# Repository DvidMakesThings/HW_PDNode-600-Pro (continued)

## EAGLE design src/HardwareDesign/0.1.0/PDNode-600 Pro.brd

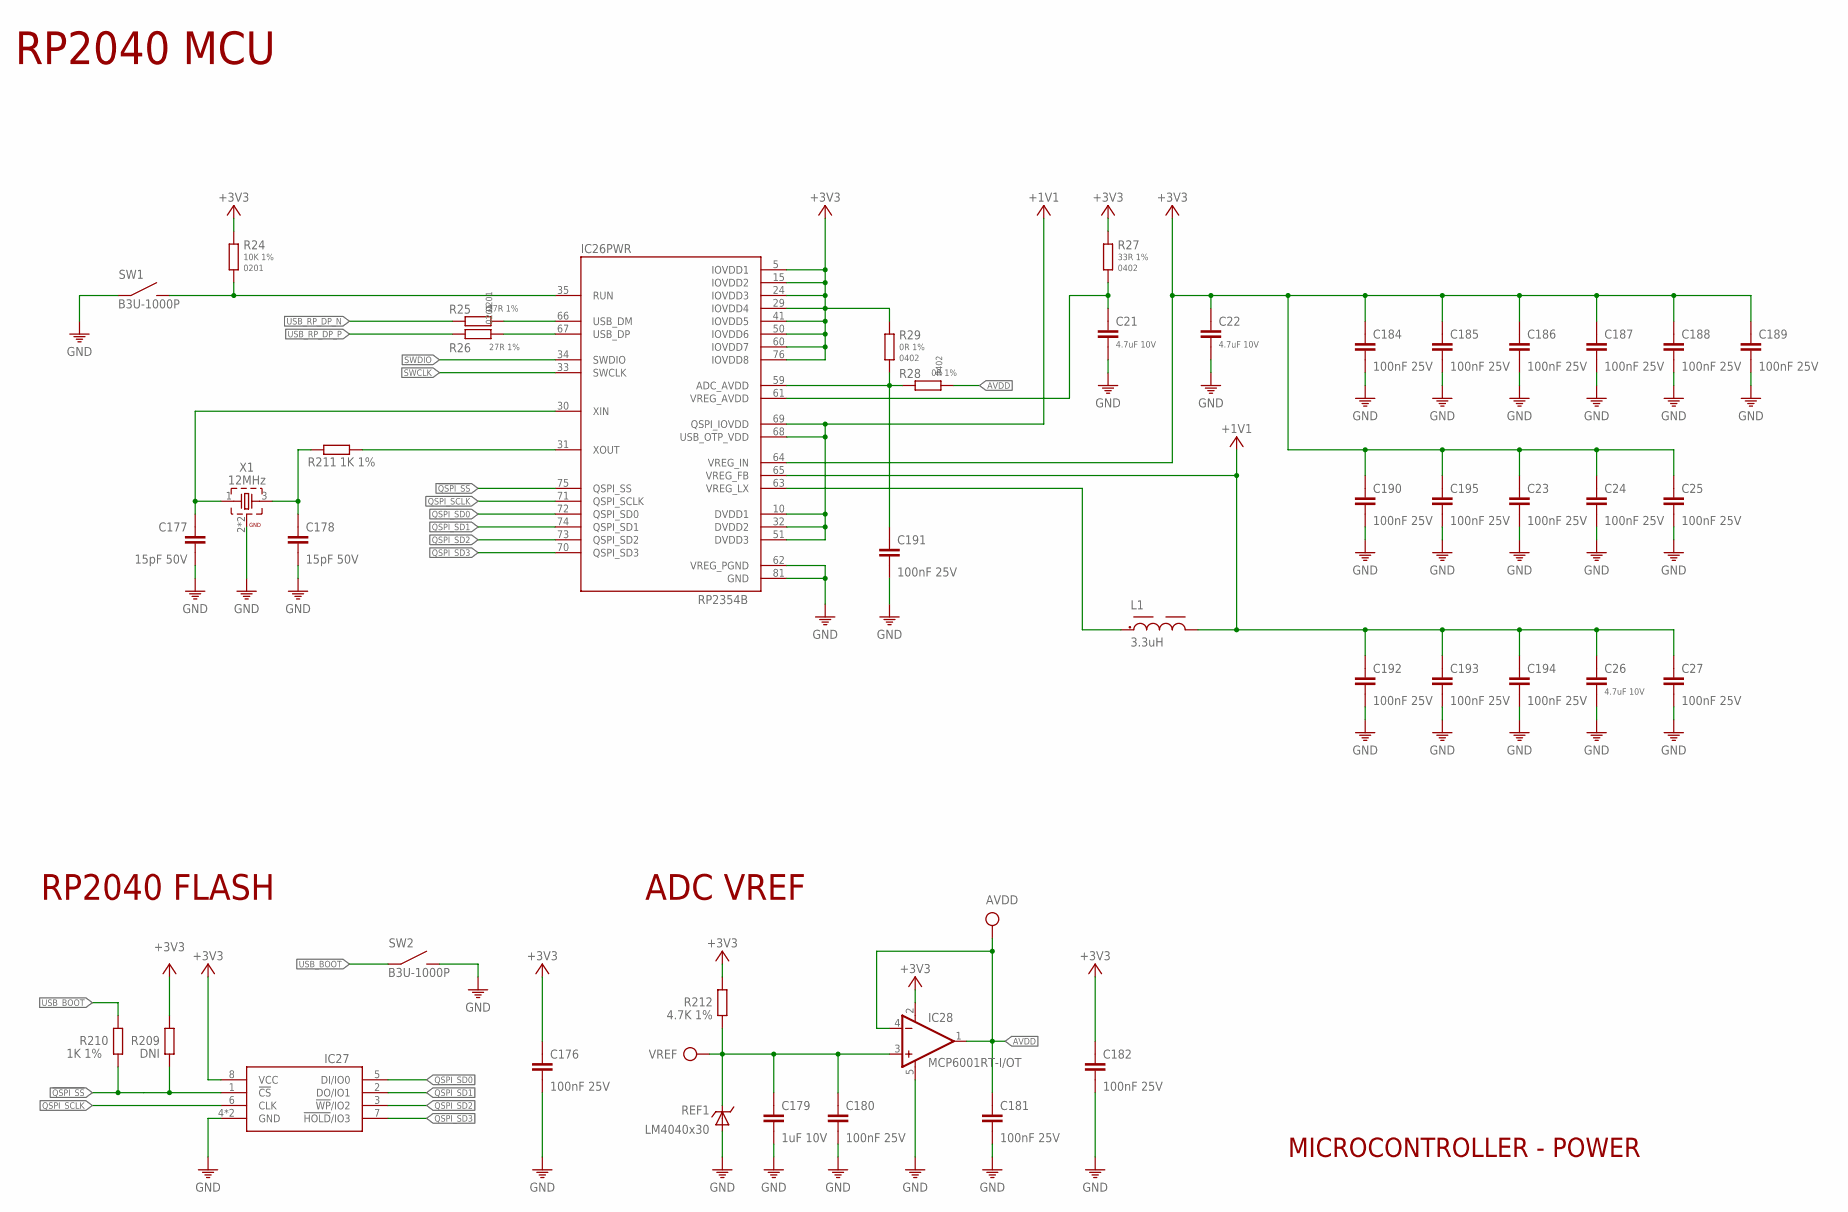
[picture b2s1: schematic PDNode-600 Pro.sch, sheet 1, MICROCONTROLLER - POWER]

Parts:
AVDD: TESTPOINT; TP
C21, C22, C26: 4.7uF 10V; 0402
C23, C24, C25, C27, C176, C180, C181, C182, C184, C185, C186, C187, C188, C189, C190, C191, C192, C193, C194, C195: 100nF 25V; 0201
C177, C178: 15pF 50V; 0201
C179: 1uF 10V; 0201
IC26: RP2354B; QFN80-10X10
IC27: W25Q128JVPIQ; SON127P600X500X75-8N
IC28: MCP6001RT-I/OT; SOT23-5
L1: 3.3uH; 0805
R24: 10K 1%; 0201
R25, R26: 27R 1%; 0201
R27: 33R 1%; 0402
R28, R29: 0R 1%; 0402
R209: DNI; R0201
R210, R211: 1K 1%; 0201
R212: 4.7K 1%; 0201
REF1: LM4040x30; SOT23
SW1, SW2: B3U-1000P
VREF: TESTPOINT; TP
X1: 12MHz; WE-XTAL_CFPX-180

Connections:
!QSPI_SS: IC26.75 (QSPI_SS), IC27.1 (!CS), R209.1, R210.2
+1V1: C26.1, C27.1, C192.1, C193.1, C194.1, IC26.10 (DVDD1), IC26.32 (DVDD2), IC26.51 (DVDD3), IC26.65 (VREG_FB), IC26.68 (USB_OTP_VDD), IC26.69 (QSPI_IOVDD), L1.2
+3V3: C22.1, C23.1, C24.1, C25.1, C176.1, C182.1, C184.1, C185.1, C186.1, C187.1, C188.1, C189.1, C190.1, C195.1, IC26.5 (IOVDD1), IC26.15 (IOVDD2), IC26.24 (IOVDD3), IC26.29 (IOVDD4), IC26.41 (IOVDD5), IC26.50 (IOVDD6), IC26.60 (IOVDD7), IC26.64 (VREG_IN), IC26.76 (IOVDD8), IC27.8 (VCC), IC28.2 (V+), R24.1, R27.1, R29.1, R209.2, R212.2; also elsewhere on the board
AVDD: AVDD.TP, C181.1, IC28.1 (OUT), IC28.4 (-IN), R28.2
GND: C21.2, C22.2, C23.2, C24.2, C25.2, C26.2, C27.2, C176.2, C177.2, C178.2, C179.2, C180.2, C181.2, C182.2, C184.2, C185.2, C186.2, C187.2, C188.2, C189.2, C190.2, C191.2, C192.2, C193.2, C194.2, C195.2, IC26.62 (VREG_PGND), IC26.81 (GND), IC27.4 (GND), IC27.PAD (GND), IC28.5 (V-), REF1.2 (A), REF1.3 (A), SW1.1, SW2.2, X1.2 (GND), X1.4 (GND); also elsewhere on the board
unnamed: IC26.35 (RUN), R24.2, SW1.2
unnamed: IC26.66 (USB_DM), R25.2
unnamed: IC26.67 (USB_DP), R26.2
unnamed: C191.1, IC26.59 (ADC_AVDD), R28.1, R29.2
unnamed: C21.1, IC26.61 (VREG_AVDD), R27.2
unnamed: IC26.63 (VREG_LX), L1.1
unnamed: C178.1, R211.1, X1.3 (2)
QSPI_SCLK: IC26.71 (QSPI_SCLK), IC27.6 (CLK)
QSPI_SD0: IC26.72 (QSPI_SD0), IC27.5 (DI/IO0)
QSPI_SD1: IC26.74 (QSPI_SD1), IC27.2 (DO/IO1)
QSPI_SD2: IC26.73 (QSPI_SD2), IC27.3 (!WP!/IO2)
QSPI_SD3: IC26.70 (QSPI_SD3), IC27.7 (!HOLD!/IO3)
RP_XI: C177.1, IC26.30 (XIN), X1.1
RP_XO: IC26.31 (XOUT), R211.2
SWCLK: IC26.33 (SWCLK)
SWDIO: IC26.34 (SWDIO)
USB_BOOT: R210.1, SW2.1
USB_RP_DP_N: R25.1
USB_RP_DP_P: R26.1
VREF: C179.1, C180.1, IC28.3 (+IN), R212.1, REF1.1 (C), VREF.TP

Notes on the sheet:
RP2040 MCU
RP2040 FLASH
ADC VREF
MICROCONTROLLER - POWER

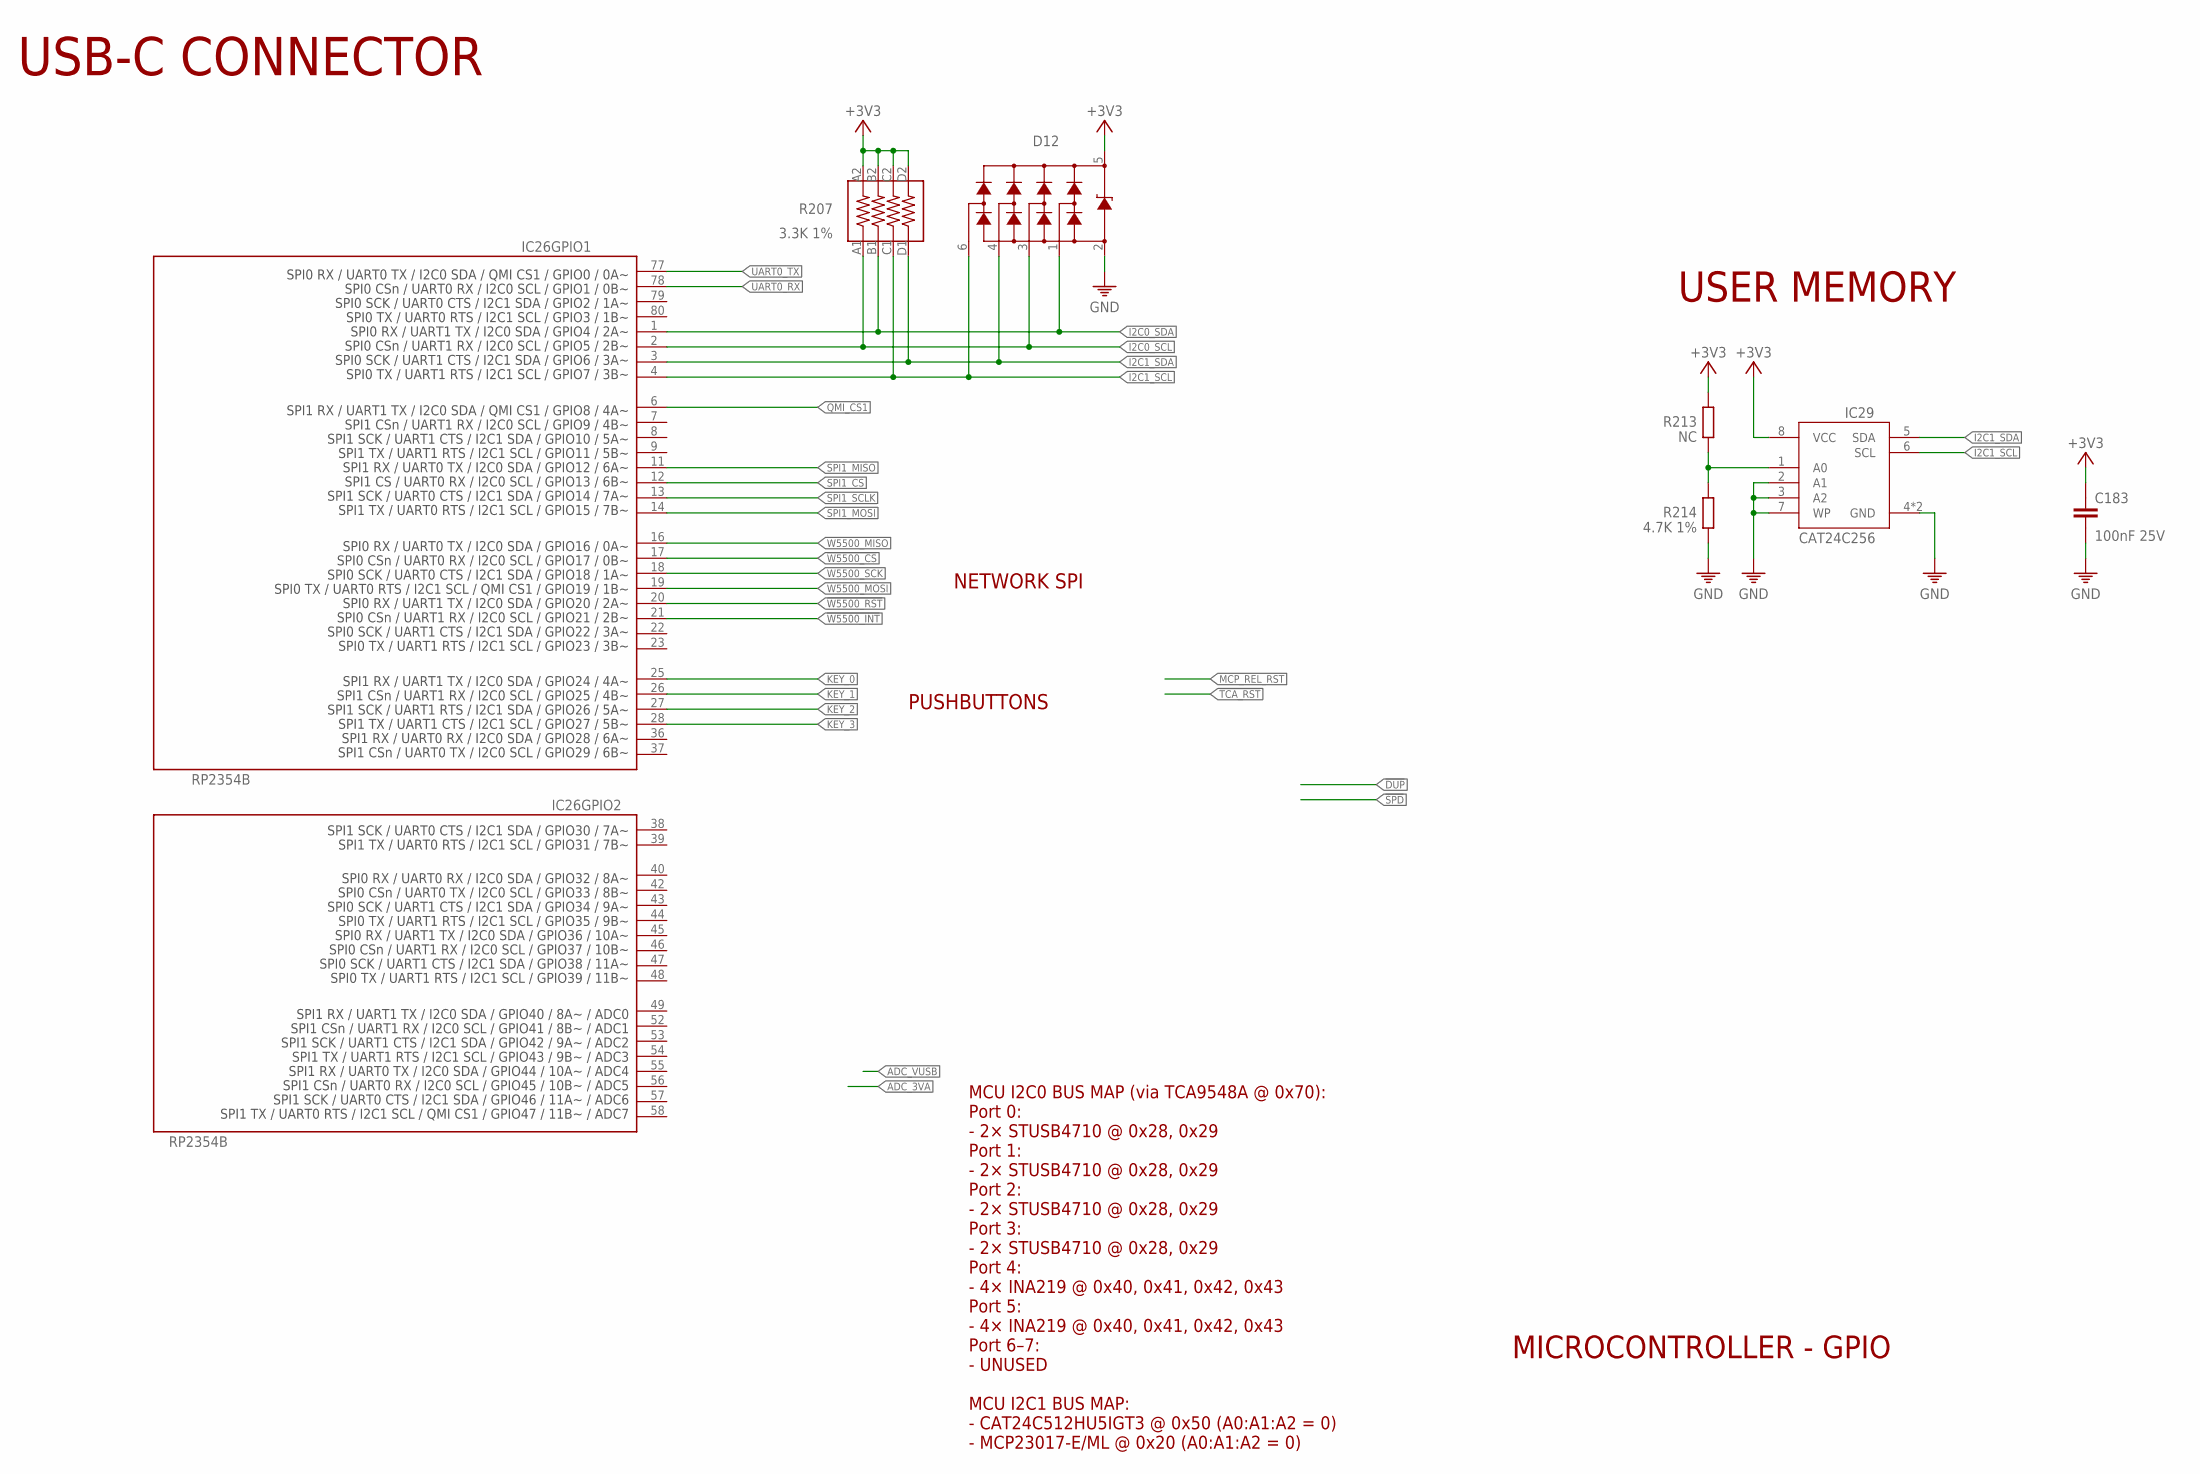
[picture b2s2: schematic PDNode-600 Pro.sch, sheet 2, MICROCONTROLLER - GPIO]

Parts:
C183: 100nF 25V; 0201
D12: HDMIULC6-4SC6Y; SOT23-6
IC26: RP2354B; QFN80-10X10
IC29: CAT24C256HU4IGT3; SON50P300X200X50-9T130X140N
R207: 3.3K 1%; _0603X4-1206
R213: NC; R0201
R214: 4.7K 1%; 0201

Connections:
!W5500_CS: IC26.17 (GPIO17); also elsewhere on the board
!W5500_INT: IC26.21 (GPIO21); also elsewhere on the board
!W5500_RST: IC26.20 (GPIO20); also elsewhere on the board
+3V3: C183.1, D12.5, IC29.8 (VCC), R207.A2 (8), R207.B2 (7), R207.C2 (6), R207.D2 (5), R213.2; also elsewhere on the board
GND: C183.2, D12.2, IC29.2 (A1), IC29.3 (A2), IC29.4 (GND), IC29.7 (WP), IC29.9 (GND), R214.1; also elsewhere on the board
I2C0_SCL: D12.3, IC26.2 (GPIO5), R207.A1 (1); also elsewhere on the board
I2C0_SDA: D12.1, IC26.1 (GPIO4), R207.B1 (2); also elsewhere on the board
I2C1_SCL: D12.6, IC26.4 (GPIO7), IC29.6 (SCL), R207.C1 (3); also elsewhere on the board
I2C1_SDA: D12.4, IC26.3 (GPIO6), IC29.5 (SDA), R207.D1 (4); also elsewhere on the board
KEY_0: IC26.25 (GPIO24); also elsewhere on the board
KEY_1: IC26.26 (GPIO25); also elsewhere on the board
KEY_2: IC26.27 (GPIO26); also elsewhere on the board
KEY_3: IC26.28 (GPIO27); also elsewhere on the board
unnamed: IC29.1 (A0), R213.1, R214.2
QMI_CS1: IC26.6 (GPIO8)
SPI1_CS: IC26.12 (GPIO13)
SPI1_MISO: IC26.11 (GPIO12)
SPI1_MOSI: IC26.14 (GPIO15)
SPI1_SCLK: IC26.13 (GPIO14)
UART0_RX: IC26.78 (GPIO1)
UART0_TX: IC26.77 (GPIO0)
W5500_MISO: IC26.16 (GPIO16); also elsewhere on the board
W5500_MOSI: IC26.19 (GPIO19); also elsewhere on the board
W5500_SCK: IC26.18 (GPIO18); also elsewhere on the board

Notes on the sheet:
USB-C CONNECTOR
NETWORK SPI
PUSHBUTTONS
MCU I2C0 BUS MAP (via TCA9548A @ 0x70): Port 0: - 2× STUSB4710 @ 0x28, 0x29 Port 1: - 2× STUSB4710 @ 0x28, 0x29 Port 2: - 2× STUSB4710 @ 0x28, 0x29 Port 3: - 2× STUSB4710 @ 0x28, 0x29 Port 4: - 4× INA219 @ 0x40, 0x41, 0x42, 0x43 Port 5: - 4× INA219 @ 0x40, 0x41, 0x42, 0x43 Port 6–7: - UNUSED MCU I2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
USER MEMORY
MICROCONTROLLER - GPIO

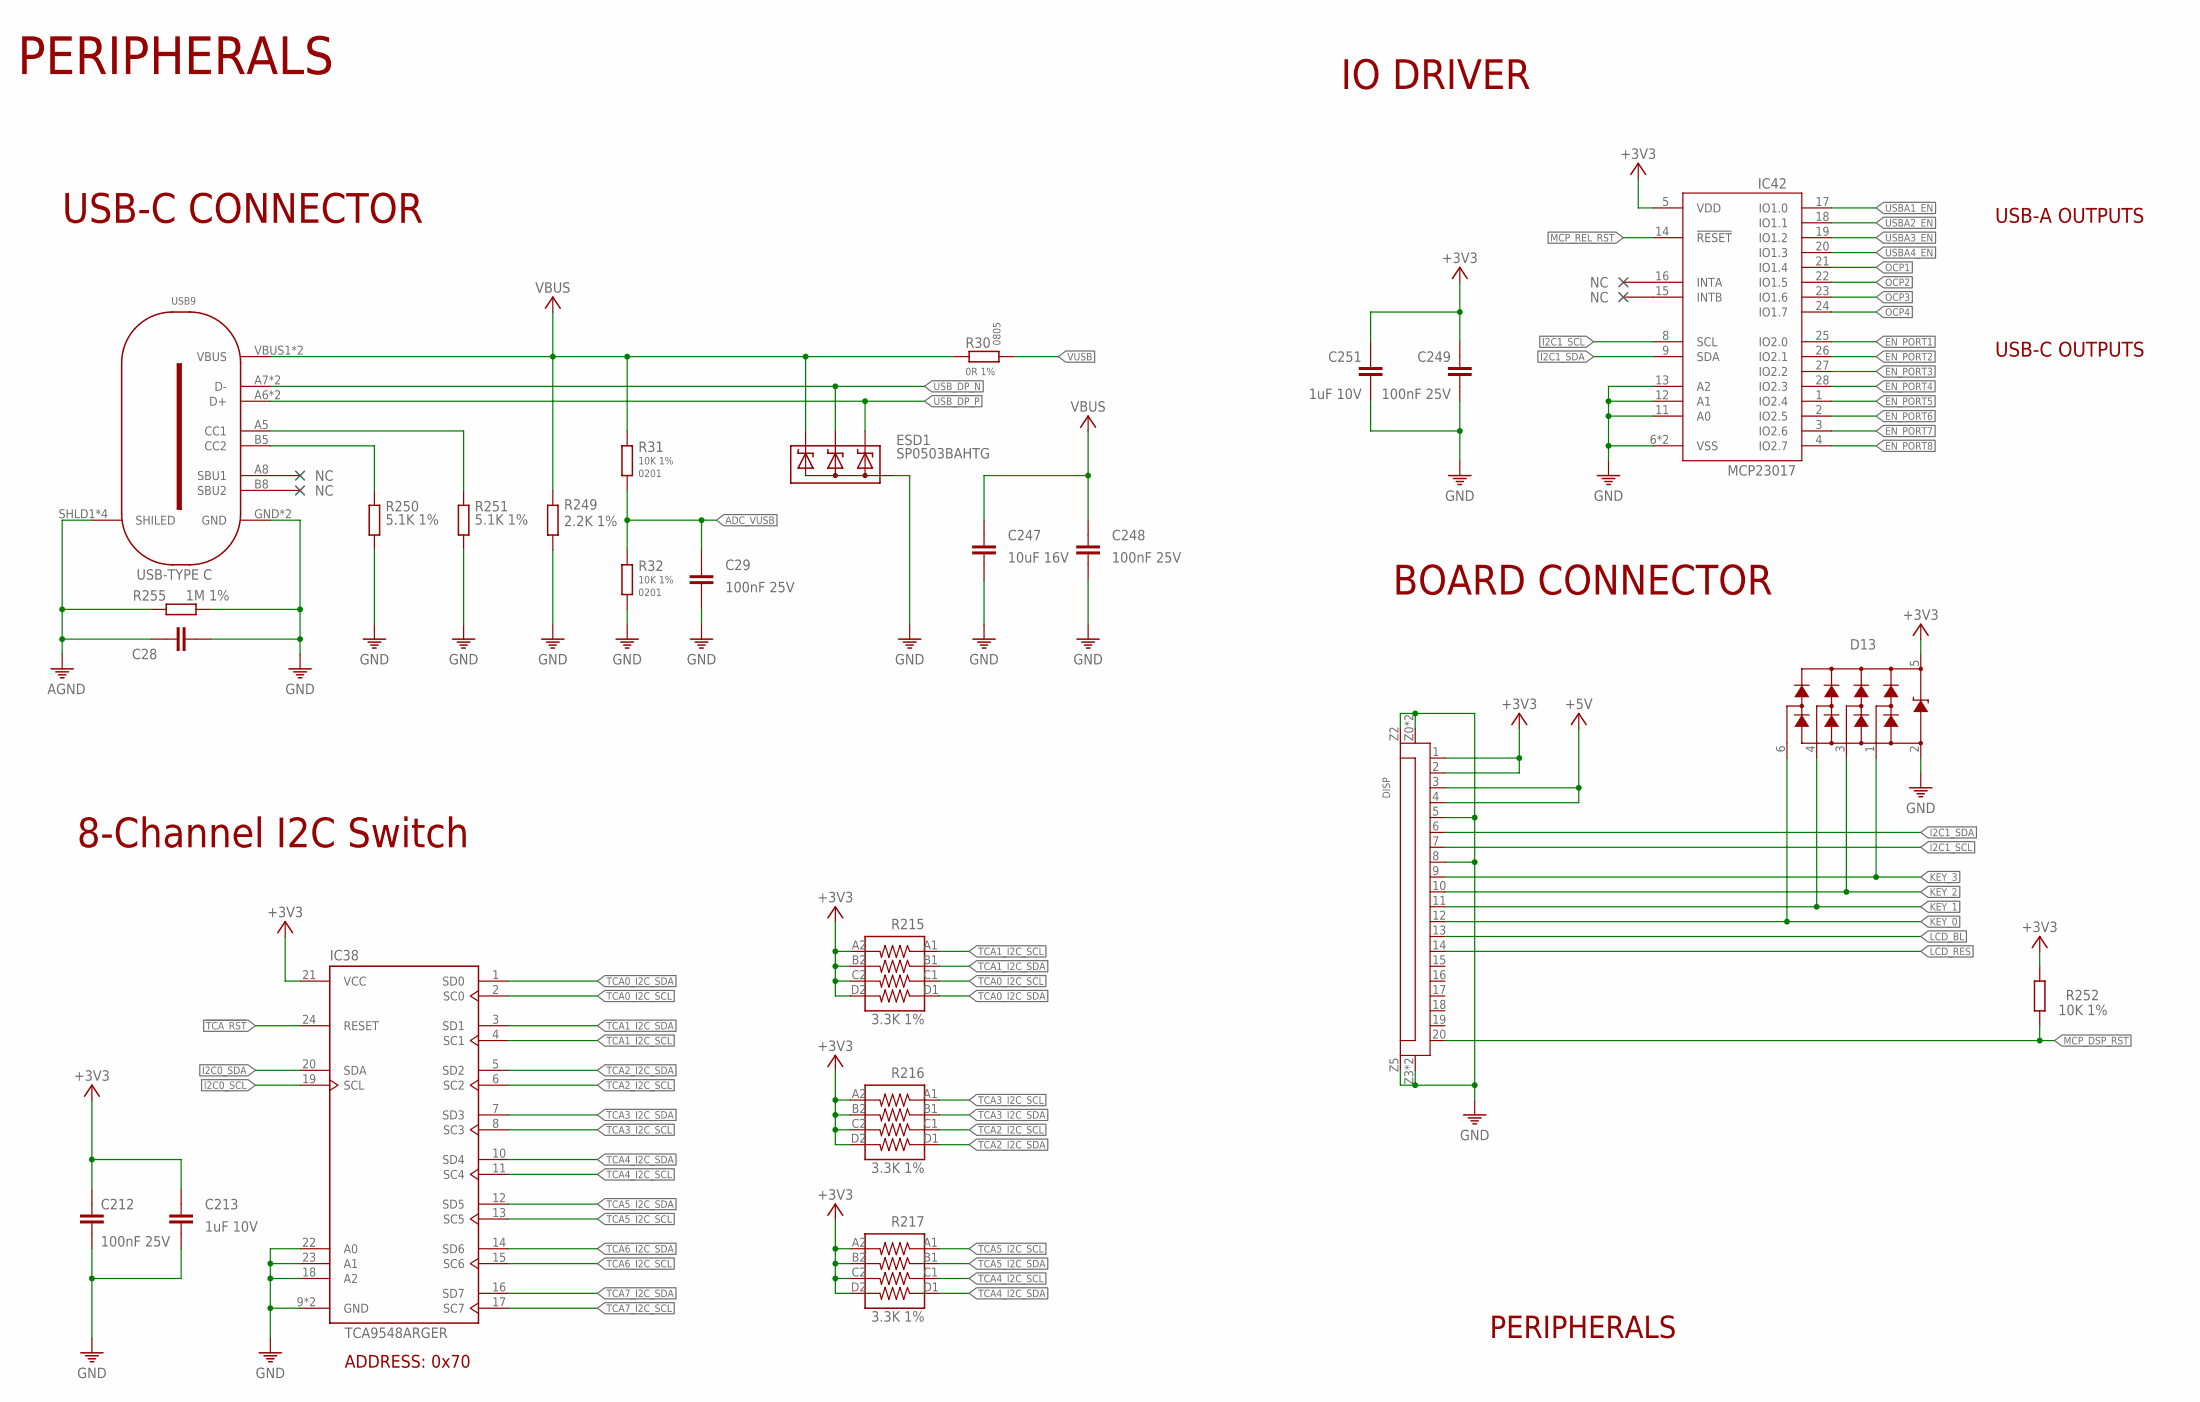
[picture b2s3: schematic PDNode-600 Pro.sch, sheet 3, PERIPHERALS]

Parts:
C28: 1NF-2KV; 1206
C29, C248: 100nF 25V; 0402
C212, C249: 100nF 25V; 0201
C213, C251: 1uF 10V; 0201
C247: 10uF 16V; 0603
D13: HDMIULC6-4SC6Y; SOT23-6
DISP: AFC11-S20ICC-00; FPC20
ESD1: SP0503BAHTG; SOT143
IC38: TCA9548ARGER; QFN50P400X400X100-25T210N
IC42: MCP23017T-E/ML; QFN28[6X6]ML
R30: 0R 1%; 0805
R31, R32, R252: 10K 1%; 0201
R215, R216, R217: 3.3K 1%; _0603X4-1206
R249: 2.2K 1%; 0201
R250, R251: 5.1K 1%; 0201
R255: 1M 1%; 0603
USB9: USB-TYPE-C-018; USB-C

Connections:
!TCA_RST: IC38.24 (RESET)
+3V3: C212.1, C213.1, C249.1, C251.1, D13.5, DISP.1, DISP.2, IC38.21 (VCC), IC42.5 (VDD), R215.A2 (8), R215.B2 (7), R215.C2 (6), R215.D2 (5), R216.A2 (8), R216.B2 (7), R216.C2 (6), R216.D2 (5), R217.A2 (8), R217.B2 (7), R217.C2 (6), R217.D2 (5), R252.2; also elsewhere on the board
+5V: DISP.3, DISP.4
ADC_VUSB: C29.1, R31.2, R32.1
AGND: C28.1, R255.1, USB9.SHLD1 (SHILED), USB9.SHLD2 (SHILED), USB9.SHLD3 (SHILED), USB9.SHLD4 (SHILED); also elsewhere on the board
CC1: R251.1, USB9.A5 (CC1)
CC2: R250.1, USB9.B5 (CC2)
EN_PORT1: IC42.25 (IO2.0); also elsewhere on the board
EN_PORT2: IC42.26 (IO2.1)
EN_PORT3: IC42.27 (IO2.2)
EN_PORT4: IC42.28 (IO2.3)
EN_PORT5: IC42.1 (IO2.4)
EN_PORT6: IC42.2 (IO2.5)
EN_PORT7: IC42.3 (IO2.6)
EN_PORT8: IC42.4 (IO2.7)
GND: C28.2, C29.2, C212.2, C213.2, C247.2, C248.2, C249.2, C251.2, D13.2, DISP.5, DISP.8, DISP.Z0 (Z1), DISP.Z1, DISP.Z2, DISP.Z3, DISP.Z4 (Z3), DISP.Z5 (Z4), ESD1.1 (A), IC38.9 (GND), IC38.18 (A2), IC38.22 (A0), IC38.23 (A1), IC38.25 (GND), IC42.6 (VSS), IC42.11 (A0), IC42.12 (A1), IC42.13 (A2), IC42.PAD (VSS), R32.2, R249.2, R250.2, R251.2, R255.2, USB9.GND, USB9.GND2 (GND); also elsewhere on the board
I2C0_SCL: IC38.19 (SCL); also elsewhere on the board
I2C0_SDA: IC38.20 (SDA); also elsewhere on the board
I2C1_SCL: DISP.7, IC42.8 (SCL); also elsewhere on the board
I2C1_SDA: DISP.6, IC42.9 (SDA); also elsewhere on the board
KEY_0: D13.6, DISP.12; also elsewhere on the board
KEY_1: D13.4, DISP.11; also elsewhere on the board
KEY_2: D13.3, DISP.10; also elsewhere on the board
KEY_3: D13.1, DISP.9; also elsewhere on the board
LCD_BL: DISP.13
LCD_RES: DISP.14
MCP_DSP_RST: DISP.20, R252.1
MCP_REL_RST: IC42.14 (!RESET)
OCP1: IC42.21 (IO1.4); also elsewhere on the board
OCP2: IC42.22 (IO1.5); also elsewhere on the board
OCP3: IC42.23 (IO1.6); also elsewhere on the board
OCP4: IC42.24 (IO1.7); also elsewhere on the board
TCA0_I2C_SCL: IC38.2 (SC0), R215.C1 (3); also elsewhere on the board
TCA0_I2C_SDA: IC38.1 (SD0), R215.D1 (4); also elsewhere on the board
TCA1_I2C_SCL: IC38.4 (SC1), R215.A1 (1)
TCA1_I2C_SDA: IC38.3 (SD1), R215.B1 (2)
TCA2_I2C_SCL: IC38.6 (SC2), R216.C1 (3)
TCA2_I2C_SDA: IC38.5 (SD2), R216.D1 (4)
TCA3_I2C_SCL: IC38.8 (SC3), R216.A1 (1)
TCA3_I2C_SDA: IC38.7 (SD3), R216.B1 (2)
TCA4_I2C_SCL: IC38.11 (SC4), R217.C1 (3); also elsewhere on the board
TCA4_I2C_SDA: IC38.10 (SD4), R217.D1 (4); also elsewhere on the board
TCA5_I2C_SCL: IC38.13 (SC5), R217.A1 (1)
TCA5_I2C_SDA: IC38.12 (SD5), R217.B1 (2)
TCA6_I2C_SCL: IC38.15 (SC6)
TCA6_I2C_SDA: IC38.14 (SD6)
TCA7_I2C_SCL: IC38.17 (SC7)
TCA7_I2C_SDA: IC38.16 (SD7)
USBA1_EN: IC42.17 (IO1.0); also elsewhere on the board
USBA2_EN: IC42.18 (IO1.1); also elsewhere on the board
USBA3_EN: IC42.19 (IO1.2); also elsewhere on the board
USBA4_EN: IC42.20 (IO1.3); also elsewhere on the board
USB_DP_N: ESD1.3 (C2), USB9.A7 (D-), USB9.B7 (D-)
USB_DP_P: ESD1.2 (C1), USB9.A6 (D+), USB9.B6 (D+)
VBUS: C247.1, C248.1, ESD1.4 (C3), R30.1, R31.1, R249.1, USB9.VBUS1 (VBUS), USB9.VBUS2 (VBUS)
VUSB: R30.2

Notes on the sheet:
PERIPHERALS
USB-C CONNECTOR
8-Channel I2C Switch
ADDRESS: 0x70
IO DRIVER
USB-A OUTPUTS
USB-C OUTPUTS
BOARD CONNECTOR

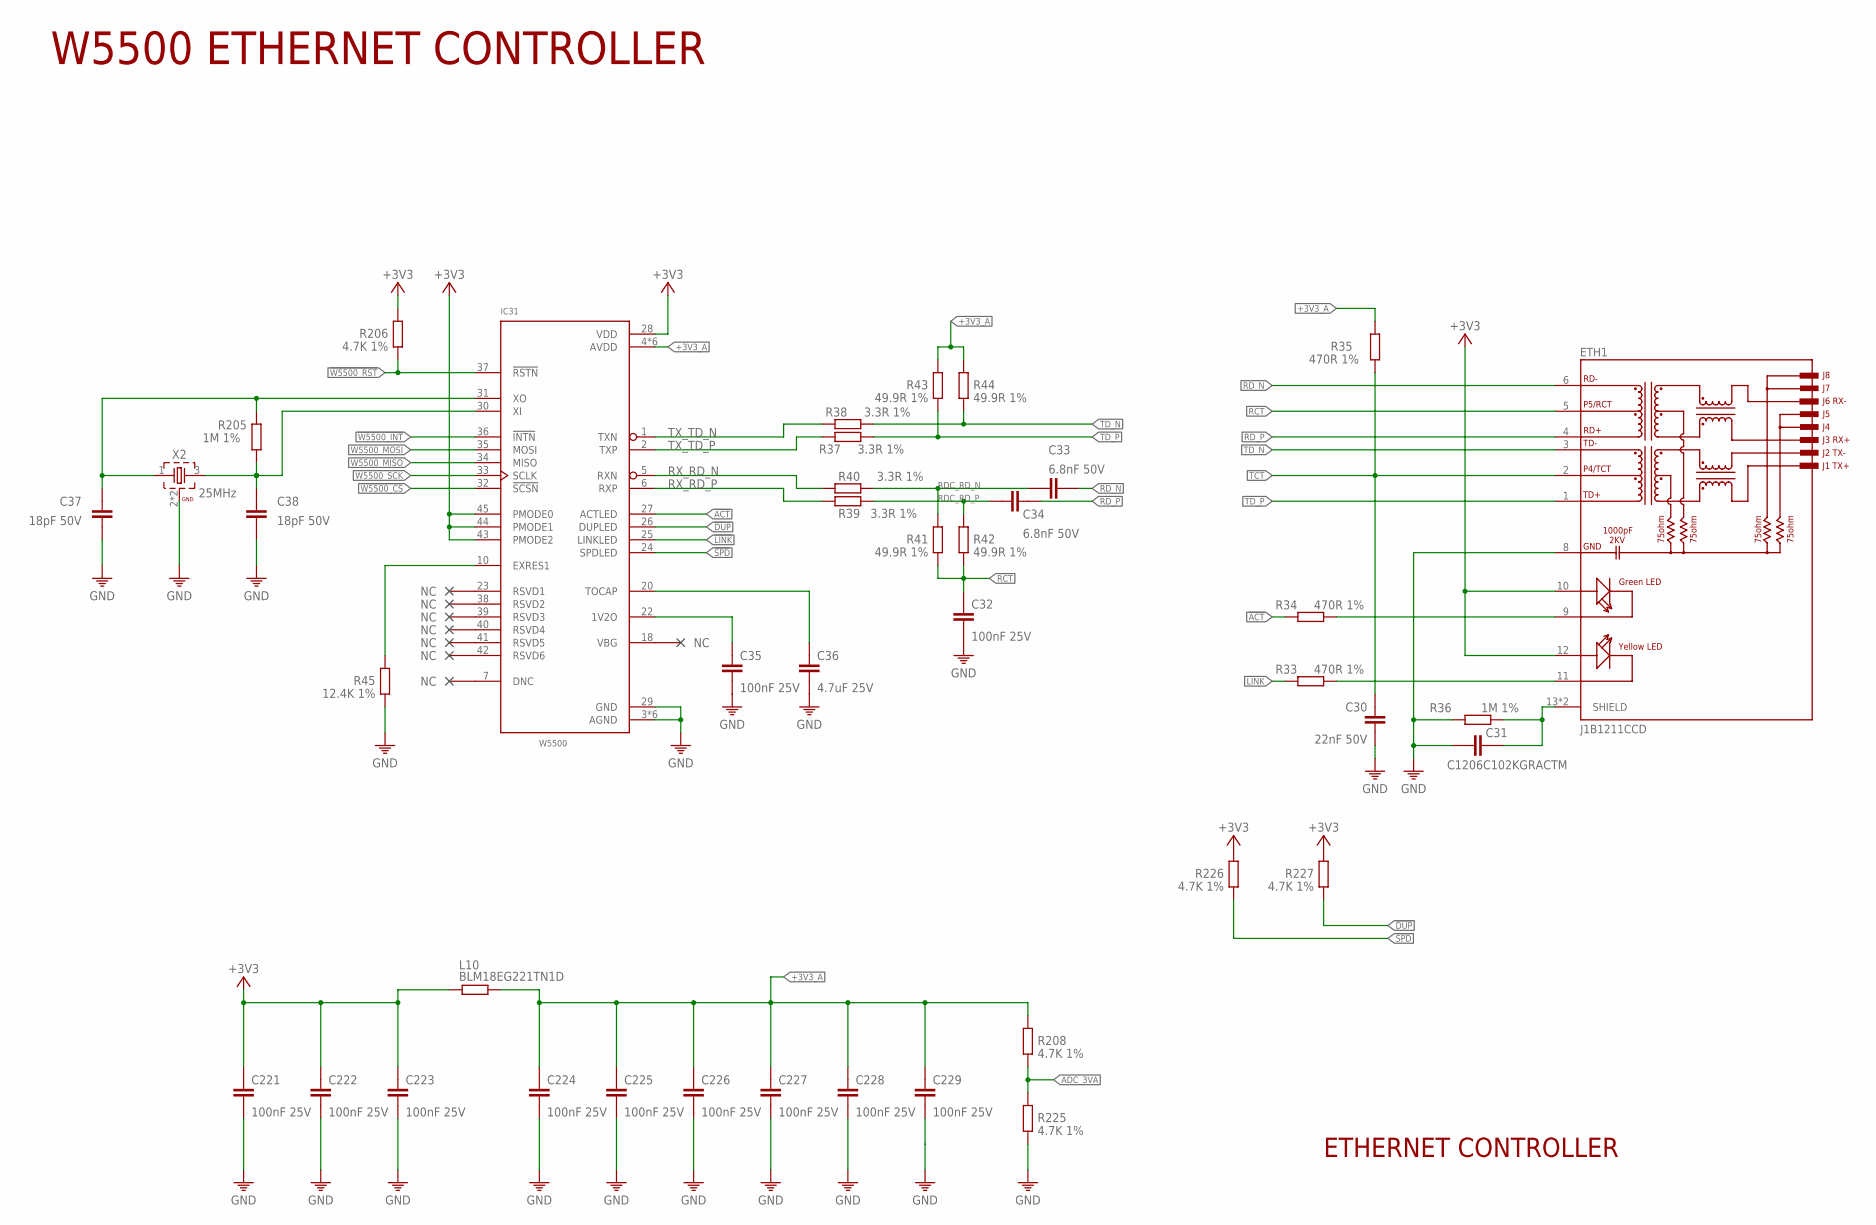
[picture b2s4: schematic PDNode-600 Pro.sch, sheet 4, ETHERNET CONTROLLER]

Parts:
C30: 22nF 50V; 0402
C31: C1206C102KGRACTM; C1206
C32: 100nF 25V; 0402
C33, C34: 6.8nF 50V; 0201
C35, C221, C222, C223, C224, C225, C226, C227, C228, C229: 100nF 25V; 0201
C36: 4.7uF 25V; 0402
C37, C38: 18pF 50V; 0201
ETH1: J1B1211CCD
IC31: W5500; LQFP48
L10: BLM18EG221TN1D; 0603
R33, R34, R35: 470R 1%; 0402
R36: 1M 1%; 1206
R37, R38, R39, R40: 3.3R 1%; 0201
R41, R42, R43, R44: 49.9R 1%; 0201
R45: 12.4K 1%; R0201
R205: 1M 1%; 0201
R206, R208, R225, R226, R227: 4.7K 1%; 0201
X2: 25MHz; WE-XTAL_CFPX-180

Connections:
!ACT: IC31.27 (ACTLED), R34.1
!DUP: IC31.26 (DUPLED), R227.1
!LINK: IC31.25 (LINKLED), R33.1
!SPD: IC31.24 (SPDLED), R226.1
!W5500_CS: IC31.32 (!SCSN); also elsewhere on the board
!W5500_INT: IC31.36 (!INTN); also elsewhere on the board
!W5500_RST: IC31.37 (!RSTN), R206.1; also elsewhere on the board
+3V3: C221.1, C222.1, C223.1, ETH1.10 (GREEN+), ETH1.12 (YELLOW+), IC31.28 (VDD), IC31.43 (PMODE2), IC31.44 (PMODE1), IC31.45 (PMODE0), L10.1, R206.2, R226.2, R227.2; also elsewhere on the board
+3V3_A: C224.1, C225.1, C226.1, C227.1, C228.1, C229.1, IC31.4 (AVDD), IC31.8 (AVDD), IC31.11 (AVDD), IC31.15 (AVDD), IC31.17 (AVDD), IC31.21 (AVDD), L10.2, R35.2, R43.2, R44.2, R208.2
ADC_3VA: R208.1, R225.2
GND: C30.2, C31.1, C32.2, C35.2, C36.2, C37.2, C38.2, C221.2, C222.2, C223.2, C224.2, C225.2, C226.2, C227.2, C228.2, C229.2, ETH1.8 (GND), IC31.3 (AGND), IC31.9 (AGND), IC31.14 (AGND), IC31.16 (AGND), IC31.19 (AGND), IC31.29 (GND), IC31.48 (AGND), R36.1, R45.1, R225.1, X2.2 (GND), X2.4 (GND); also elsewhere on the board
unnamed: ETH1.11 (YELLOW-), R33.2
unnamed: ETH1.9 (GREEN-), R34.2
unnamed: IC31.10 (EXRES1), R45.2
unnamed: C35.1, IC31.22 (1V2O)
unnamed: C36.1, IC31.20 (TOCAP)
unnamed: C38.1, IC31.30 (XI), R205.1, X2.3 (2)
RCT: C32.1, ETH1.5 (P5/RCT), R41.1, R42.1
RDC_RD_N: C33.1, R40.2, R41.2
RDC_RD_P: C34.1, R39.2, R42.2
RD_N: C33.2, ETH1.6 (RD-)
RD_P: C34.2, ETH1.4 (RD+)
RX_RD_N: IC31.5 (RXN), R40.1
RX_RD_P: IC31.6 (RXP), R39.1
SH: C31.2, ETH1.13 (SHIELD), ETH1.14 (SHIELD), R36.2
TCT: C30.1, ETH1.2 (P4/TCT), R35.1
TD_N: ETH1.3 (TD-), R38.2, R44.1
TD_P: ETH1.1 (TD+), R37.2, R43.1
TX_TD_N: IC31.1 (TXN), R38.1
TX_TD_P: IC31.2 (TXP), R37.1
W5500_MISO: IC31.34 (MISO); also elsewhere on the board
W5500_MOSI: IC31.35 (MOSI); also elsewhere on the board
W5500_SCK: IC31.33 (SCLK); also elsewhere on the board
XO: C37.1, IC31.31 (XO), R205.2, X2.1

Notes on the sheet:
W5500 ETHERNET CONTROLLER
ETHERNET CONTROLLER

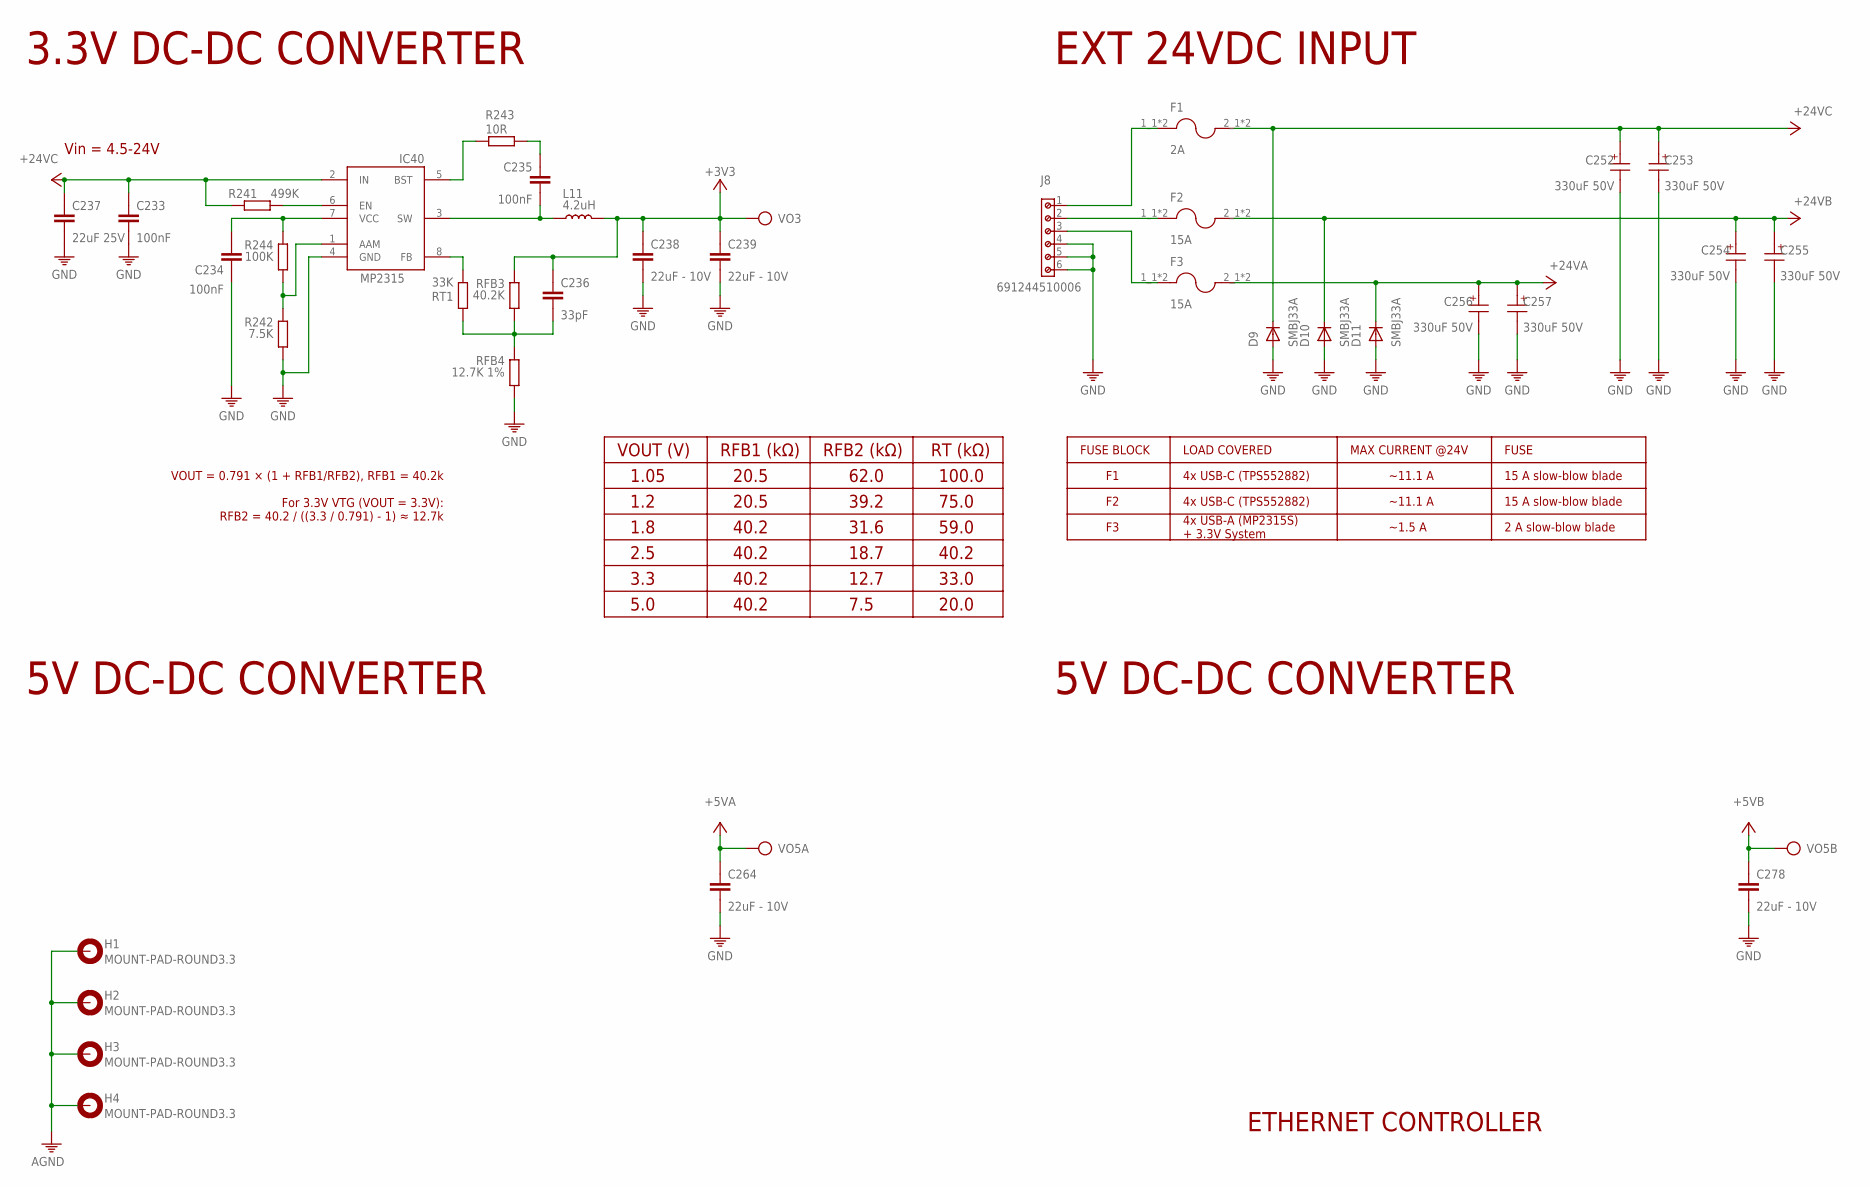
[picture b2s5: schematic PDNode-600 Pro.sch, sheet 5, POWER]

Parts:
C233, C234, C235: 100nF; 0201
C236: 33pF; 0201
C237: 22uF 25V; C1206
C238, C239, C264, C278: 22uF - 10V; C1206
C252, C253, C254, C255, C256, C257: 330uF 50V; 10X10.5(DXL)
D9, D10, D11: SMBJ33A; SMB
F1: 2A; FUSE_3544-2
F2, F3: 15A; FUSE_3544-2
H1, H2, H3, H4: MOUNT-PAD-ROUND3.3; 3,3-PAD
IC40: MP2315GJ-Z; SOT65P280X110-8N
J8: 691244510006
L11: 4.2uH; SRR5228A
R241: 499K; R0201
R242: 7.5K; R0201
R243: 10R; R0201
R244: 100K; R0201
RFB3: 40.2K; R0201
RFB4: 12.7K 1%; R0201
RT1: 33K; R0201
VO3, VO5A, VO5B: TESTPOINT; TP

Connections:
3V3_EN_SYS1: IC40.6 (EN), R241.2
24VINA: F2.1_1 (1), F2.1_2 (1), J8.2
24VINB: F3.1_1 (1), F3.1_2 (1), J8.3
24VINC: F1.1_1 (1), F1.1_2 (1), J8.1
+3V3: C236.1, C238.1, C239.1, L11.2, RFB3.1, VO3.TP; also elsewhere on the board
+5VA: C264.1, VO5A.TP; also elsewhere on the board
+5VB: C278.1, VO5B.TP; also elsewhere on the board
+24V_A: C256.1 (+), C257.1 (+), D11.C, F3.2_1 (2), F3.2_2 (2); also elsewhere on the board
+24V_B: C254.1 (+), C255.1 (+), D10.C, F2.2_1 (2), F2.2_2 (2)
+24V_C: C233.1, C237.1, C252.1 (+), C253.1 (+), D9.C, F1.2_1 (2), F1.2_2 (2), IC40.2 (IN), R241.1
AGND: H1.B3,3, H2.B3,3, H3.B3,3, H4.B3,3; also elsewhere on the board
GND: C233.2, C234.2, C237.2, C238.2, C239.2, C252.2 (-), C253.2 (-), C254.2 (-), C255.2 (-), C256.2 (-), C257.2 (-), C264.2, C278.2, D9.A, D10.A, D11.A, IC40.4 (GND), J8.4, J8.5, J8.6, R242.2, RFB4.2; also elsewhere on the board
unnamed: IC40.5 (BST), R243.2
unnamed: IC40.8 (FB), RT1.1
unnamed: C235.2, IC40.3 (SW), L11.1
unnamed: C235.1, R243.1
unnamed: C236.2, RFB3.2, RFB4.1, RT1.2
unnamed: C234.1, IC40.7 (VCC), R244.1
unnamed: IC40.1 (AAM), R242.1, R244.2

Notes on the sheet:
VOUT = 0.791 × (1 + RFB1/RFB2), RFB1 = 40.2k For 3.3V VTG (VOUT = 3.3V): RFB2 = 40.2 / ((3.3 / 0.791) - 1) ≈ 12.7k
VOUT (V)
EXT 24VDC INPUT
FUSE BLOCK
LOAD COVERED
MAX CURRENT @24V
FUSE
4x USB-C (TPS552882)
4x USB-A (MP2315S) + 3.3V System
~11.1 A
~1.5 A
15 A slow-blow blade
2 A slow-blow blade
RFB1 (kΩ)
RFB2 (kΩ)
RT (kΩ)
1.05
1.2
1.8
3.3
5.0
20.5
40.2
62.0
39.2
31.6
18.7
12.7
7.5
2.5
100.0
75.0
59.0
33.0
20.0
3.3V DC-DC CONVERTER
Vin = 4.5-24V
5V DC-DC CONVERTER
ETHERNET CONTROLLER
